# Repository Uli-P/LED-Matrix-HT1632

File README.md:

--- work in progress ---
<br>
PCB ordered today, 06.10.2014, at dirty pcbs
<br>
see http://dirtypcbs.com/view.php?share=2058&accesskey=2a689cab1304aab6307b2c241c448fc4
<br>
This is hardware for a HT1632C LED matrix driver, an optional driver and a common cathode or common anode led 60x60mm led matrix.<br>
SJ1 - according to the datasheet you can connect the chip's OSP pin either to GND or VCCIO, don't know for what it's good<br>
SJ2 - connect to VCCIO if you drive the logic side from separate power, else to VCC<br>
SJ3 - connect to VCC if you have a common anode matrix, to GND if common cathode<br>

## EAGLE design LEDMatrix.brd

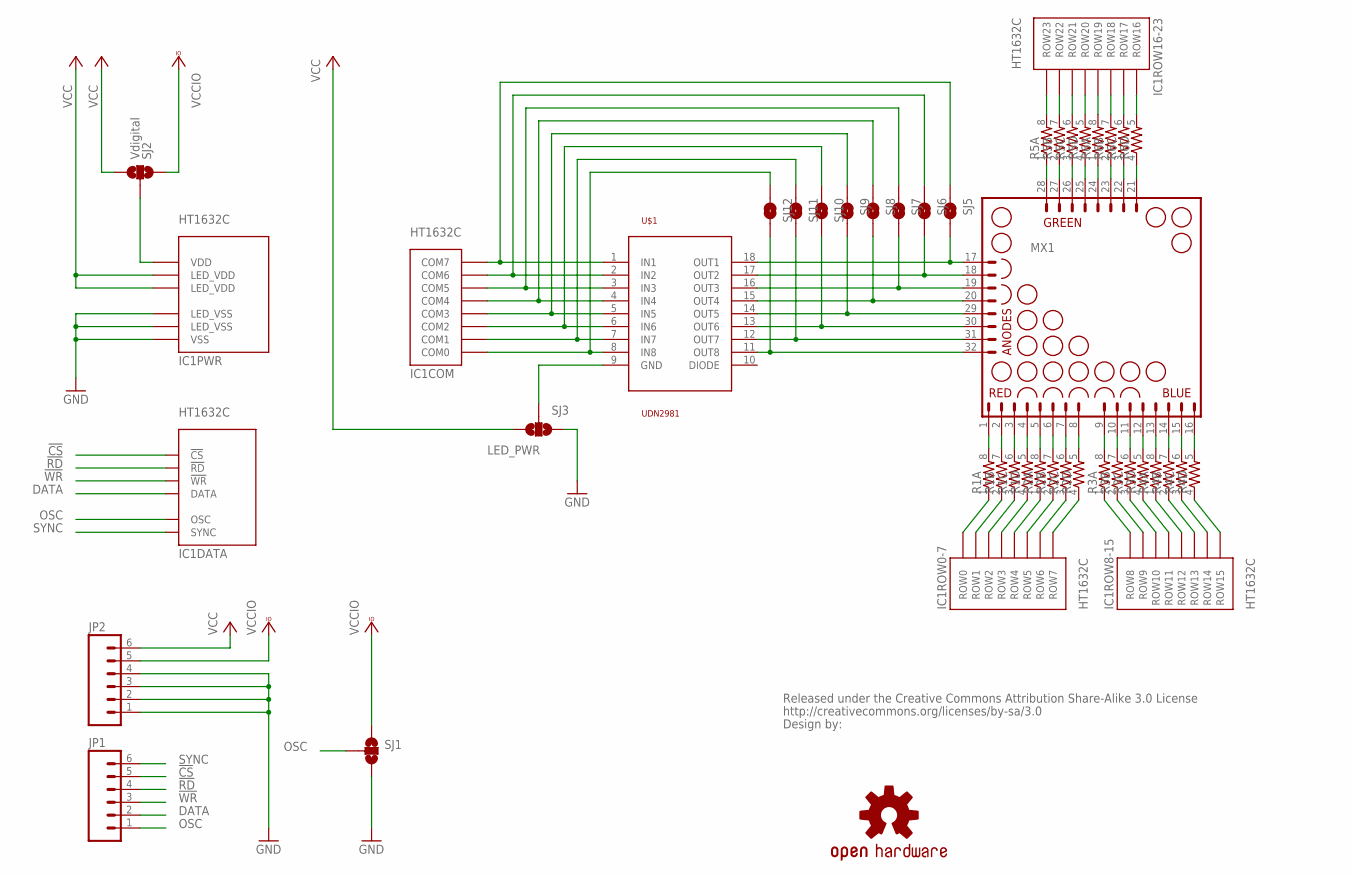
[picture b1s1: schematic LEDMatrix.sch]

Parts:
CC_TEXT1: CREATIVE_COMMONS
IC1: HT1632C; QFP52
JP1, JP2: M06SIP; 1X06
LOGO1: OSHW-LOGOL; OSHW-LOGO-L
MX1: MATRIX_8X8_TRICOLOR_ANODE_ROW; MATRIX_60MM_32PIN
R1, R2, R3, R4, R5, R6: RESISTOR-ARRAY0603-ARV; 0603-ARV
SJ1: SOLDERJUMPER_2WAY-OLDS; SJ_3
SJ2: Vdigital; SJ_3
SJ3: LED_PWR; SJ_3
SJ5, SJ6, SJ7, SJ8, SJ9, SJ10, SJ11, SJ12: SOLDERJUMPER-OLDNO; SJ_2S-NO
U$1: UDN2981; SO18L

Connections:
!CS: IC1.P$19 (!CS), JP1.5
!RD: IC1.P$18 (!RD), JP1.4
!WR: IC1.P$17 (!WR), JP1.3
COM0: IC1.P$22 (COM0), SJ12.1, U$1.8 (IN8)
COM1: IC1.P$23 (COM1), SJ11.1, U$1.7 (IN7)
COM2: IC1.P$24 (COM2), SJ10.1, U$1.6 (IN6)
COM3: IC1.P$26 (COM3), SJ9.1, U$1.5 (IN5)
COM4: IC1.P$27 (COM4), SJ8.1, U$1.4 (IN4)
COM5: IC1.P$28 (COM5), SJ7.1, U$1.3 (IN3)
COM6: IC1.P$29 (COM6), SJ6.1, U$1.2 (IN2)
COM7: IC1.P$30 (COM7), SJ5.1, U$1.1 (IN1)
DATA: IC1.P$16 (DATA), JP1.2
GND: IC1.P$14 (VSS), IC1.P$25 (LED_VSS), IC1.P$36 (LED_VSS), JP2.1, JP2.2, JP2.3, JP2.4, SJ1.3, SJ3.1
unnamed: MX1.32, SJ12.2, U$1.11 (OUT8)
unnamed: MX1.31, SJ11.2, U$1.12 (OUT7)
unnamed: MX1.30, SJ10.2, U$1.13 (OUT6)
unnamed: MX1.29, SJ9.2, U$1.14 (OUT5)
unnamed: MX1.20, SJ8.2, U$1.15 (OUT4)
unnamed: MX1.19, SJ7.2, U$1.16 (OUT3)
unnamed: MX1.18, SJ6.2, U$1.17 (OUT2)
unnamed: MX1.17, SJ5.2, U$1.18 (OUT1)
unnamed: IC1.P$21 (VDD), SJ2.2
unnamed: MX1.1, R1.8 (2)
unnamed: MX1.2, R1.7 (2)
unnamed: MX1.3, R1.6 (2)
unnamed: MX1.4, R1.5 (2)
unnamed: MX1.5, R2.8 (2)
unnamed: MX1.6, R2.7 (2)
unnamed: MX1.7, R2.6 (2)
unnamed: MX1.8, R2.5 (2)
unnamed: MX1.9, R3.8 (2)
unnamed: MX1.10, R3.7 (2)
unnamed: MX1.11, R3.6 (2)
unnamed: MX1.12, R3.5 (2)
unnamed: MX1.13, R4.8 (2)
unnamed: MX1.14, R4.7 (2)
unnamed: MX1.15, R4.6 (2)
unnamed: MX1.16, R4.5 (2)
unnamed: MX1.28, R5.1
unnamed: MX1.27, R5.2 (1)
unnamed: MX1.26, R5.3 (1)
unnamed: MX1.25, R5.4 (1)
unnamed: MX1.24, R6.1
unnamed: MX1.23, R6.2 (1)
unnamed: MX1.22, R6.3 (1)
unnamed: MX1.21, R6.4 (1)
OSC: IC1.P$15 (OSC), JP1.1, SJ1.2
ROW0: IC1.P$13 (ROW0), R1.1
ROW1: IC1.P$12 (ROW1), R1.2 (1)
ROW2: IC1.P$11 (ROW2), R1.3 (1)
ROW3: IC1.P$10 (ROW3), R1.4 (1)
ROW4: IC1.P$9 (ROW4), R2.1
ROW5: IC1.P$8 (ROW5), R2.2 (1)
ROW6: IC1.P$6 (ROW6), R2.3 (1)
ROW7: IC1.P$5 (ROW7), R2.4 (1)
ROW8: IC1.P$4 (ROW8), R3.1
ROW9: IC1.P$3 (ROW9), R3.2 (1)
ROW10: IC1.P$2 (ROW10), R3.3 (1)
ROW11: IC1.P$1 (ROW11), R3.4 (1)
ROW12: IC1.P$52 (ROW12), R4.1
ROW13: IC1.P$51 (ROW13), R4.2 (1)
ROW14: IC1.P$50 (ROW14), R4.3 (1)
ROW15: IC1.P$49 (ROW15), R4.4 (1)
ROW16: IC1.P$48 (ROW16), R6.5 (2)
ROW17: IC1.P$47 (ROW17), R6.6 (2)
ROW18: IC1.P$46 (ROW18), R6.7 (2)
ROW19: IC1.P$45 (ROW19), R6.8 (2)
ROW20: IC1.P$44 (ROW20), R5.5 (2)
ROW21: IC1.P$43 (ROW21), R5.6 (2)
ROW22: IC1.P$42 (ROW22), R5.7 (2)
ROW23: IC1.P$41 (ROW23), R5.8 (2)
SYNC: IC1.P$20 (SYNC), JP1.6
VCC: IC1.P$7 (LED_VDD), IC1.P$38 (LED_VDD), JP2.6, SJ2.3, SJ3.3
VCCIO: JP2.5, SJ1.1, SJ2.1
VLED: SJ3.2, U$1.9 (GND)

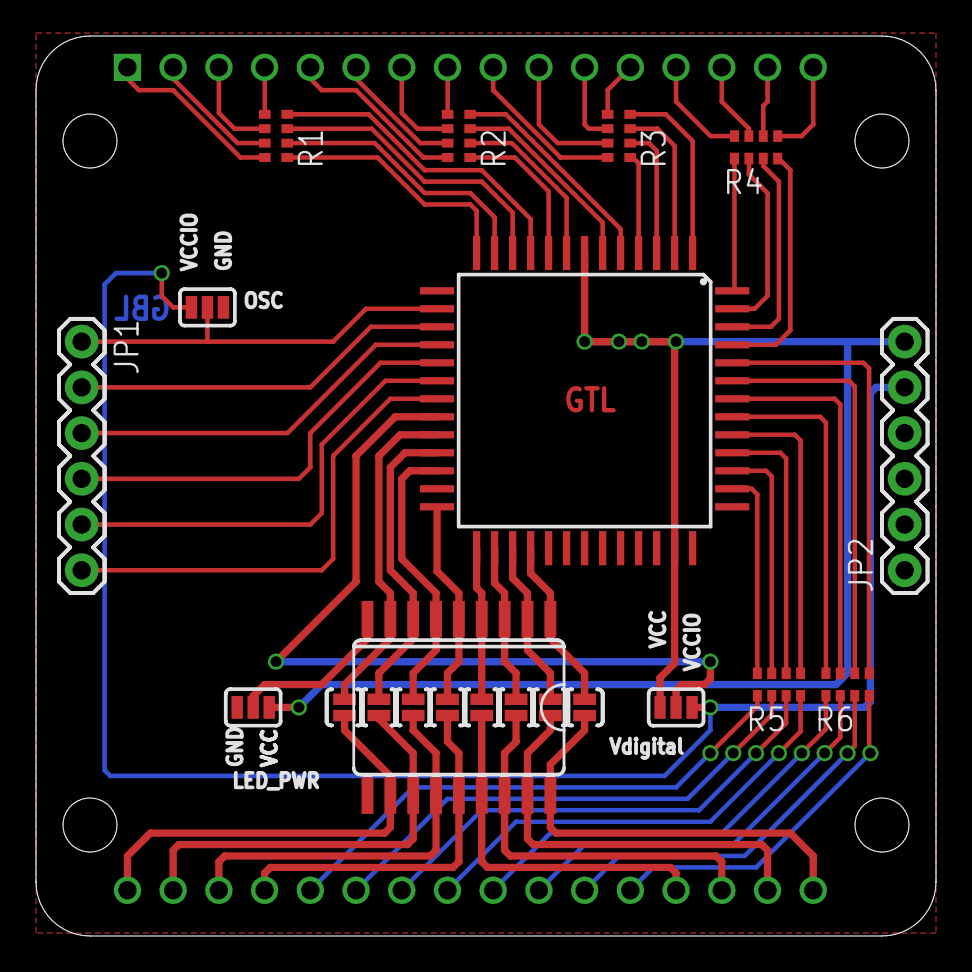
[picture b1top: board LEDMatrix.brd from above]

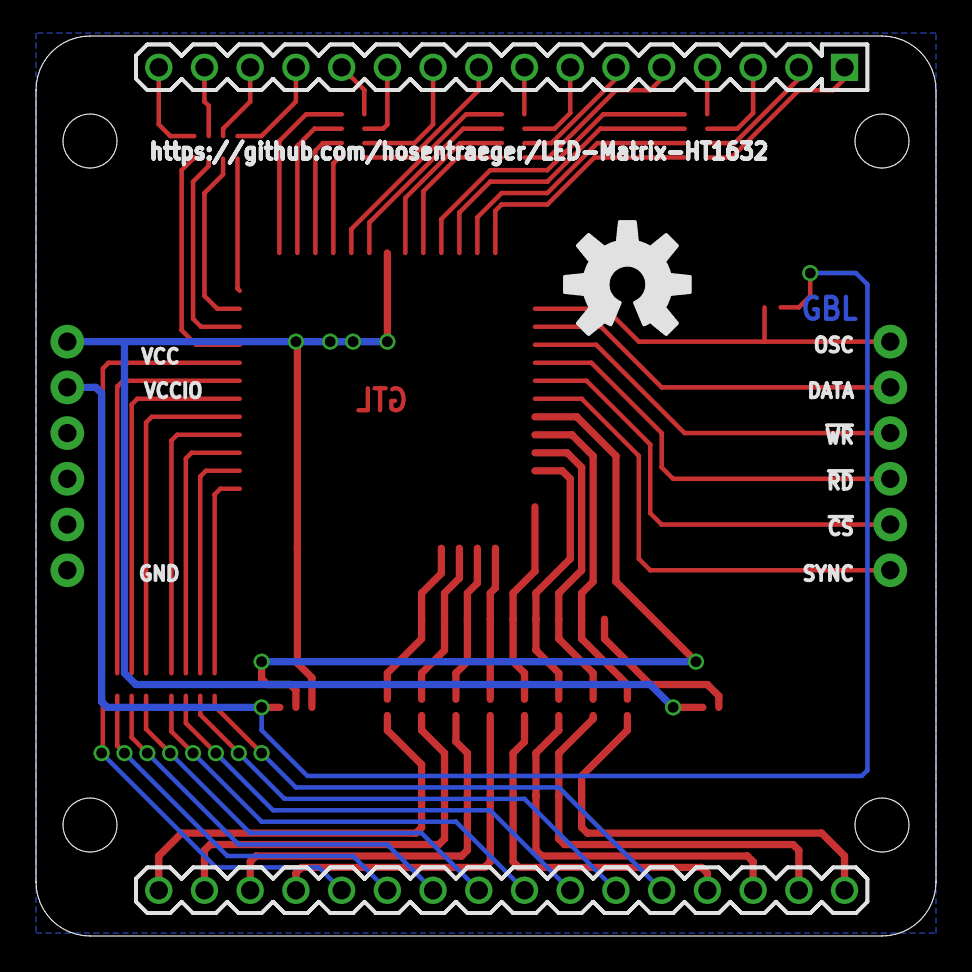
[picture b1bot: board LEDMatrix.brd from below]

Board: 2 copper layers, 50.0 x 50.0 mm, 24 parts (2 on the bottom side), 75 nets.

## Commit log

2014-09-21 fixed README
2014-09-21 added datasheets
2014-09-27 updated documentation
2014-09-27 updated silk layer
2014-10-06 added reference to dirty pcbs
2014-10-06 replaced parts library (schematic only)
2014-10-06 added parts library

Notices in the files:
parts and their libraries:
matrix: Designs by Ed Halley.  Released into the Creative Commons, with Attribution-Only, Share-Alike.
SparkFun-Passives: Licensing: CC v3.0 Share-Alike You are welcome to use this library for commercial purposes.
SparkFun-Aesthetics: http://creativecommons.org/licenses/by-sa/3.0
